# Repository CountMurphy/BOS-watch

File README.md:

Brotherhood of Steel Watch
========================

Ad Victoriam brother!

The BOS watch is the second version of my GPS enabled wristwatches. Stripped of the non used features and annoyances of the [Pipman](https://random-hackery.net/post/pipman-gps-watch/) , the BOS watch contains all things a man traveling the wastes could want

[Official Page](https://random-hackery.net/post/bos-watch/)

Features
---------------
- GPS time syncing - get local time anywhere on earth at power up

- Tilt compensated compass (with LED directional indicators and exact heading information)

- Stop watch / countdown timer

- Speaker (Plays the fallout theme!)

- TV B-gone

- A Frickn' Laser!&trade;

- Low power usage

- USB charging

-  Gieger Counter sound emulator (planned at least)

- Retro look and feel using custom DIP switches (with 7 operating modes) and 1970's era calculator display bubble LEDs

Tech
---------
The BOS watch uses an arm processor and C (Huzzah! No more awful propeller spin code)

License
----------
[DBAD](https://github.com/philsturgeon/dbad/blob/master/LICENSE-en.md)

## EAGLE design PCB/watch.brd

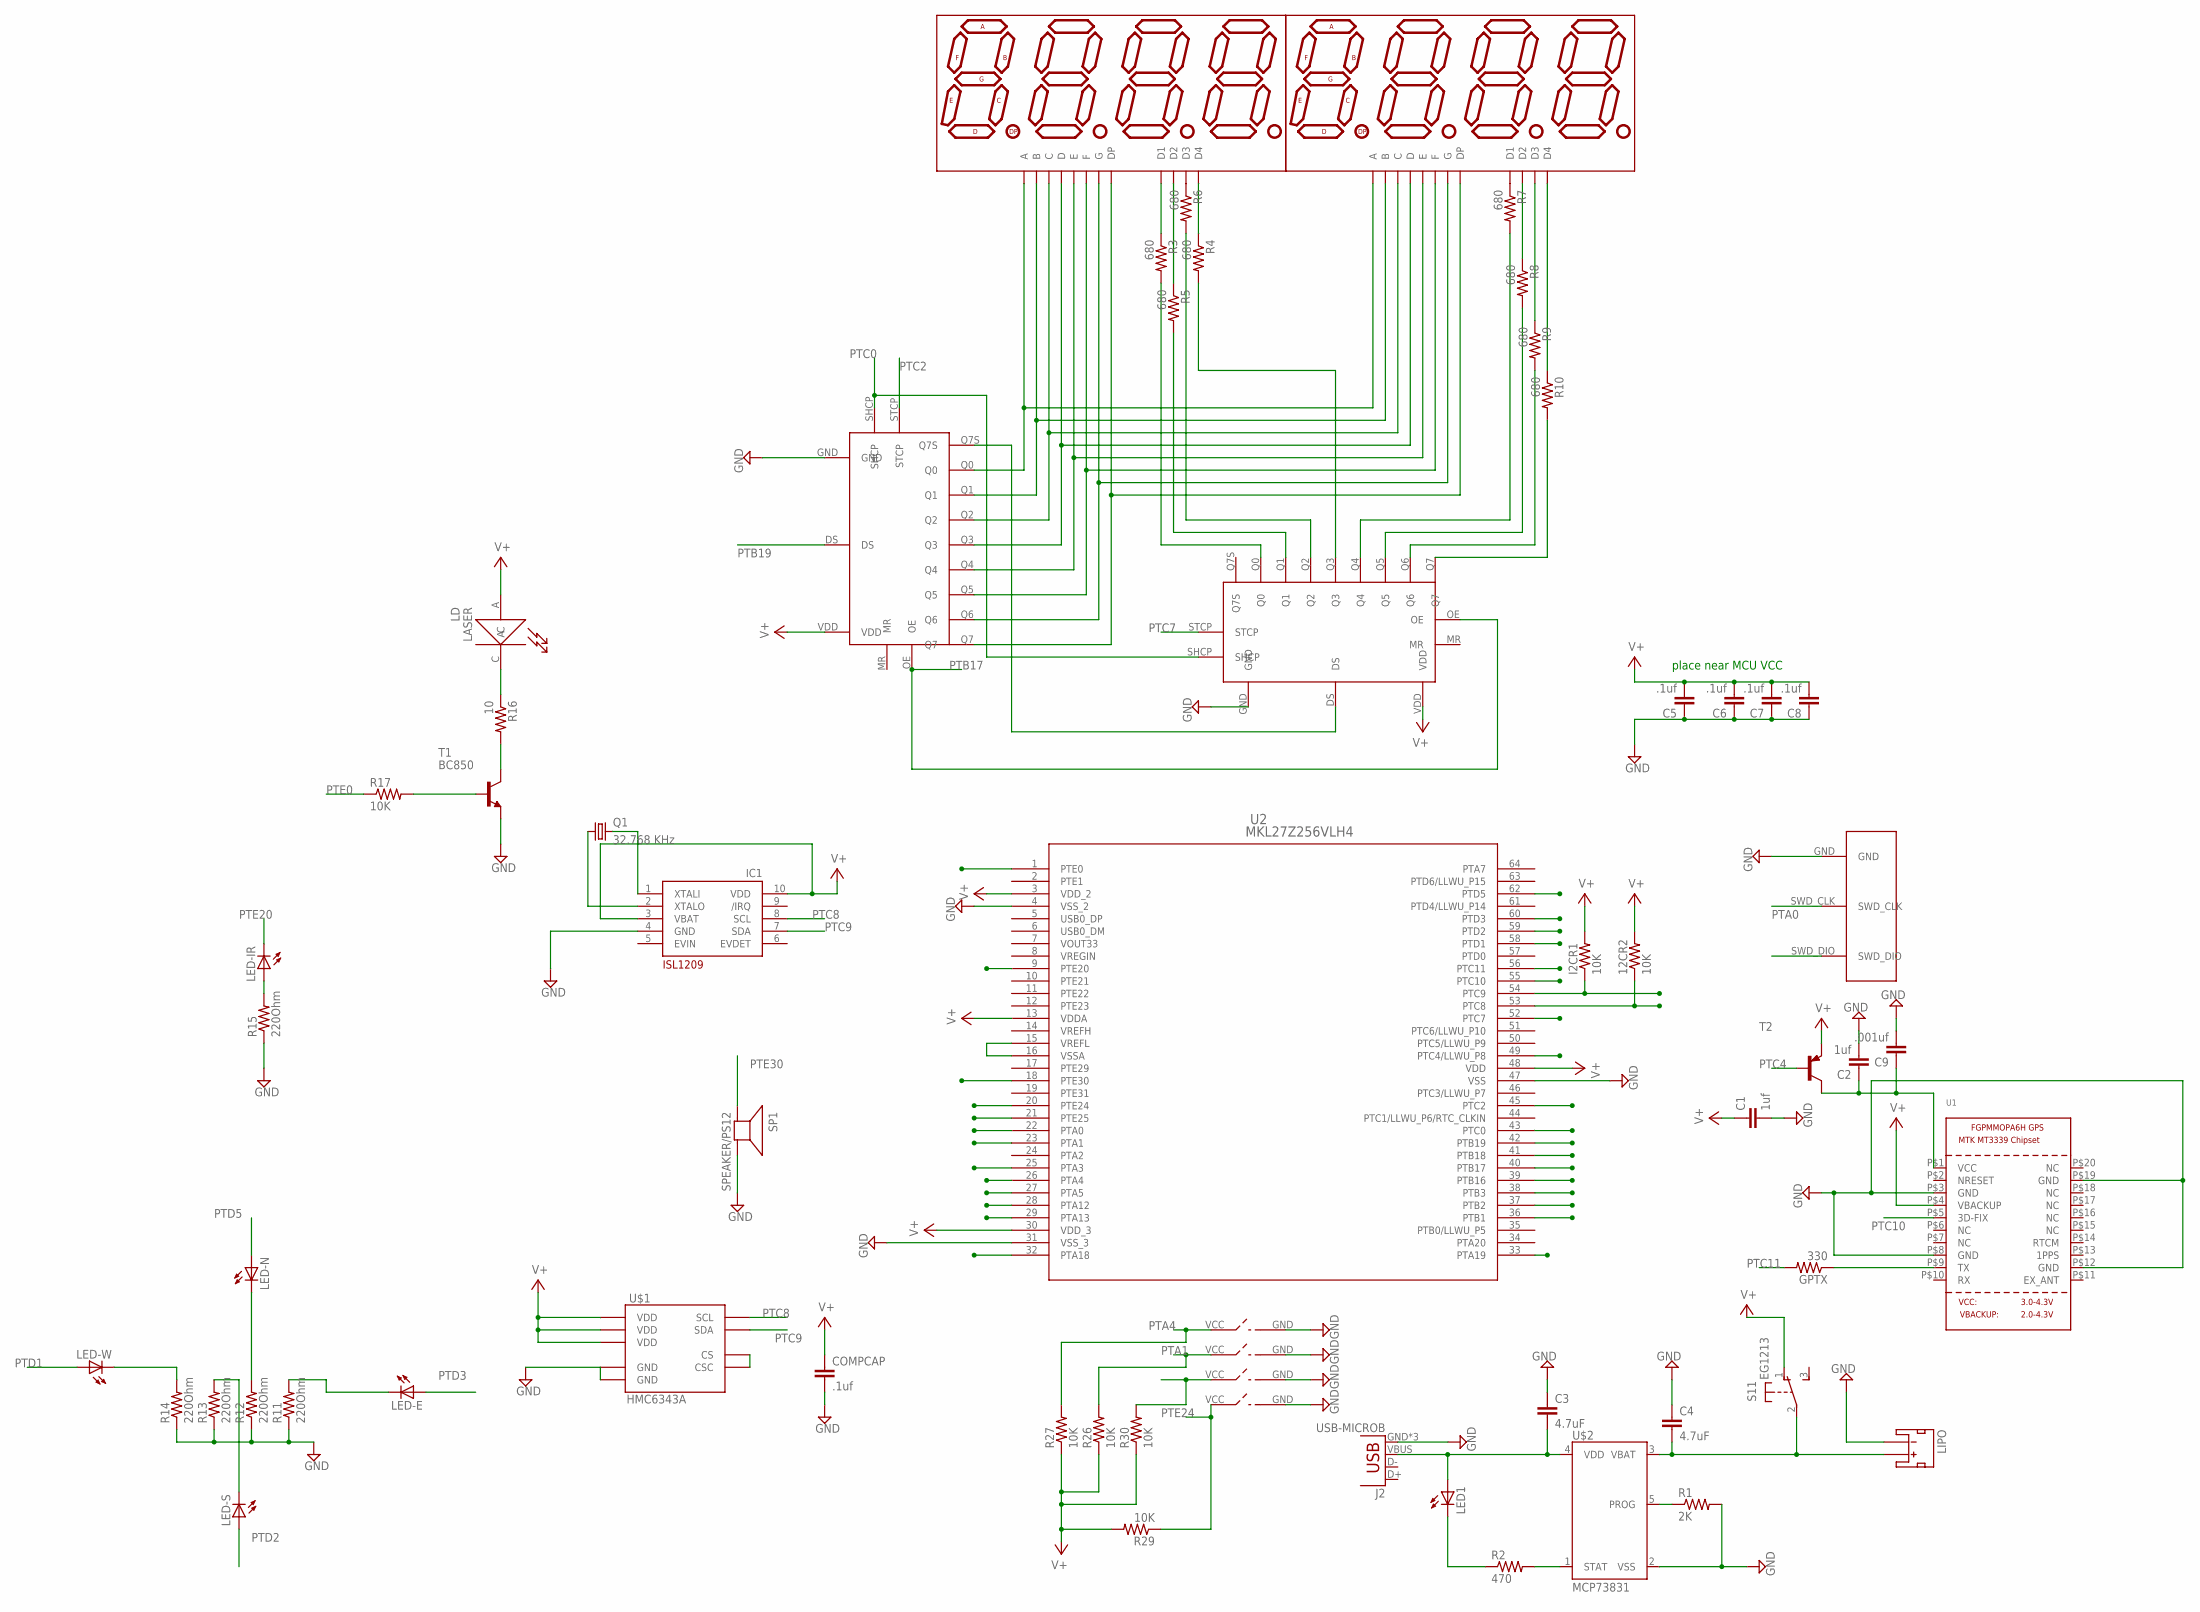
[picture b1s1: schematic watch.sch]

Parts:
12CR2: 10K; 0603-RES
C1, C2: 1uf; 0603
C3, C4: 4.7uF; 0603-CAP
C5, C6, C7, C8: .1uf; 0603
C9: .001uf; 0603
COMPCAP: .1uf; 0603
DISP1, DISP2: 7-SEGMENT-4DIGIT-COUNTER-HP-BUBBLE; DIL12
GPTX: 330; 0603-RES
I2CR1: 10K; 0603-RES
IC1: ISL1209; MSOP10
J2: USB-MICROB
LASER: LD; LD-FLUSH-WITH-JUMPER
LED1: LED_ESML0603; LED_SML0603
LED-E: LED5MM
LED-IR: LED5MM
LED-N: LED5MM
LED-S: LED5MM
LED-W: LED5MM
LIPO: JST_2MM_MALE; JST-2-SMD
Q1: 32.768 KHz; TC26H
R1: 2K; 0603-RES
R2: 470; 0603-RES
R3, R4, R5, R6, R7, R8, R9, R10: 680; 0603-RES
R11, R12, R13, R14, R15: 220Ohm; 0603-RES
R16: 10; 0603-RES
R17, R26, R27, R29, R30: 10K; 0603-RES
S1: EG1213
SP1: SPEAKER/PS12; PS12
SWD_BREAKOUT: SWD_BREAKOUTS; SWD
T1: BC850; SOT23
T2: -PNP-SOT23-EBC; SOT23-EBC
U1: GPS_FGPMMOPA6H; FGPMMOPA6H
U2: MKL27Z256VLH4; LQFP-64_10X10X1.6
U$1: HMC6343A; LCC36
U$2: MCP73831; SOT23-5
U$3, U$7, U$8, U$9: DIPS
U$4, U$5: 74HC595PW

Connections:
GND: C1.2, C2.2, C3.1, C4.1, C5.1, C6.1, C7.1, C8.1, C9.2, COMPCAP.2, IC1.4 (GND), J2.GND, J2.MT1 (GND), J2.MT2 (GND), LIPO.1 (-), R1.2, R11.1, R12.1, R13.1, R14.1, R15.1, SP1.P$2 (-), SWD_BREAKOUT.GND, T1.2 (E), U1.P$3 (GND), U1.P$8 (GND), U1.P$12 (GND), U1.P$19 (GND), U2.4 (VSS_2), U2.31 (VSS_3), U2.47 (VSS), U$1.25 (GND), U$1.29 (GND), U$2.2 (VSS), U$3.GND, U$4.GND, U$5.GND, U$7.GND, U$8.GND, U$9.GND
unnamed: U$1.22 (CS), U$1.35 (CSC)
unnamed: U2.15 (VREFL), U2.16 (VSSA)
unnamed: C4.2, LIPO.2 (+), S1.2, U$2.3 (VBAT)
unnamed: C3.2, J2.VBUS, LED1.A, U$2.4 (VDD)
unnamed: LED1.C, R2.1
unnamed: C2.1, C9.1, T2.C, U1.P$1 (VCC)
unnamed: R2.2, U$2.1 (STAT)
unnamed: R1.1, U$2.5 (PROG)
unnamed: DISP1.1 (D1), R3.1
unnamed: DISP1.10 (D2), R5.1
unnamed: DISP1.12 (A), DISP2.12 (A), U$4.Q0
unnamed: DISP1.4 (D3), R6.1
unnamed: DISP1.6 (D4), R4.1
unnamed: DISP2.1 (D1), R7.1
unnamed: DISP2.10 (D2), R8.1
unnamed: DISP1.7 (G), DISP2.7 (G), U$4.Q6
unnamed: DISP1.5 (DP), DISP2.5 (DP), U$4.Q7
unnamed: R9.2, U$5.Q6
unnamed: DISP1.9 (F), DISP2.9 (F), U$4.Q5
unnamed: DISP2.4 (D3), R9.1
unnamed: DISP1.8 (D), DISP2.8 (D), U$4.Q3
unnamed: R8.2, U$5.Q5
unnamed: R7.2, U$5.Q4
unnamed: R4.2, U$5.Q3
unnamed: R6.2, U$5.Q2
unnamed: DISP2.6 (D4), R10.1
unnamed: R3.2, U$5.Q0
unnamed: U$4.Q7S, U$5.DS
unnamed: R10.2, U$5.Q7
unnamed: GPTX.1, U1.P$9 (TX)
unnamed: R5.2, U$5.Q1
unnamed: LED-N.K (C), R12.2
unnamed: LED-E.K (C), R11.2
unnamed: LED-W.K (C), R14.2
unnamed: LED-S.K (C), R13.2
unnamed: LED-IR.A, R15.2
unnamed: LASER.C, R16.1
unnamed: R16.2, T1.3 (C)
unnamed: R17.2, T1.1 (B)
unnamed: IC1.1 (XTALI), Q1.2
unnamed: IC1.2 (XTALO), Q1.1
unnamed: DISP1.2 (E), DISP2.2 (E), U$4.Q4
unnamed: DISP1.11 (B), DISP2.11 (B), U$4.Q1
unnamed: DISP1.3 (C), DISP2.3 (C), U$4.Q2
PTA0: SWD_BREAKOUT.SWD_CLK, U2.22 (PTA0)
PTA1: R26.2, U2.23 (PTA1), U$7.VCC (V)
PTA3: SWD_BREAKOUT.SWD_DIO, U2.25 (PTA3)
PTA4: R27.2, U2.26 (PTA4), U$3.VCC (V)
PTA5: U2.27 (PTA5)
PTA12: U2.28 (PTA12)
PTA13: U2.29 (PTA13)
PTA18: U2.32 (PTA18)
PTA19: U2.33 (PTA19)
PTB1: U2.36 (PTB1)
PTB2: U2.37 (PTB2)
PTB3: U2.38 (PTB3)
PTB16: U2.39 (PTB16)
PTB17: U2.40 (PTB17), U$4.OE, U$5.OE
PTB18: U2.41 (PTB18)
PTB19: U2.42 (PTB19), U$4.DS
PTC0: U2.43 (PTC0), U$4.SHCP, U$5.SHCP
PTC2: U2.45 (PTC2), U$4.STCP
PTC4: T2.B, U2.49 (PTC4/LLWU_P8)
PTC7: U2.52 (PTC7), U$5.STCP
PTC8: 12CR2.1, IC1.8 (SCL), U2.53 (PTC8), U$1.32 (SCL)
PTC9: I2CR1.1, IC1.7 (SDA), U2.54 (PTC9), U$1.36 (SDA)
PTC10: U1.P$5 (3D-FIX), U2.55 (PTC10)
PTC11: GPTX.2, U2.56 (PTC11)
PTD1: LED-W.A, U2.58 (PTD1)
PTD2: LED-S.A, U2.59 (PTD2)
PTD3: LED-E.A, U2.60 (PTD3)
PTD5: LED-N.A, U2.62 (PTD5)
PTE0: R17.1, U2.1 (PTE0)
PTE20: LED-IR.K (C), U2.9 (PTE20)
PTE24: R29.1, U2.20 (PTE24), U$9.VCC (V)
PTE25: R30.2, U2.21 (PTE25), U$8.VCC (V)
PTE30: SP1.P$1 (+), U2.18 (PTE30)
V+: 12CR2.2, C1.1, C5.2, C6.2, C7.2, C8.2, COMPCAP.1, I2CR1.2, IC1.3 (VBAT), IC1.10 (VDD), LASER.A, R26.1, R27.1, R29.2, R30.1, S1.1 (O), T2.E, U1.P$4 (VBACKUP), U2.3 (VDD_2), U2.13 (VDDA), U2.30 (VDD_3), U2.48 (VDD), U$1.3 (VDD), U$1.11 (VDD), U$1.21 (VDD), U$4.VDD, U$5.VDD
VREFH: U2.14 (VREFH)

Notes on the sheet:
place near MCU VCC

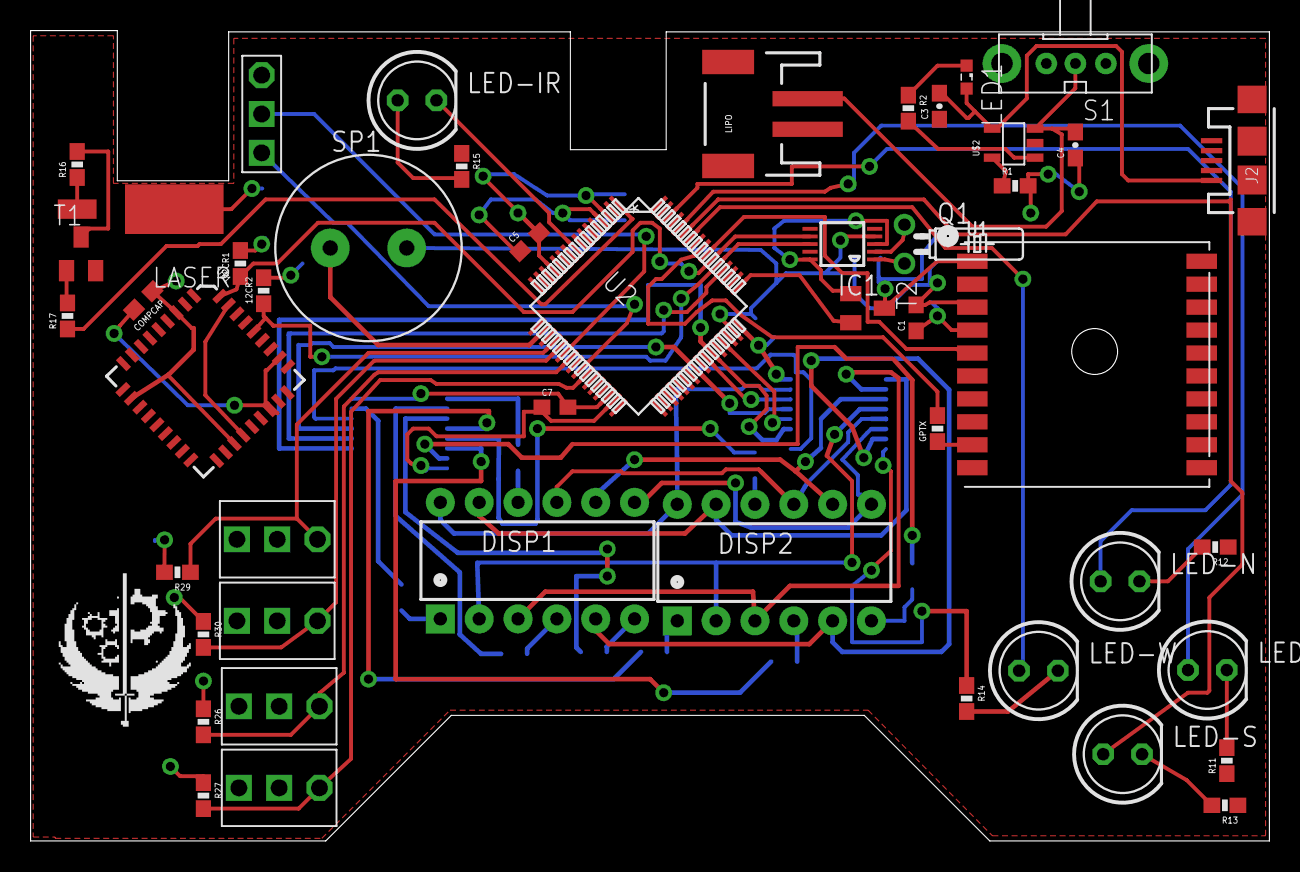
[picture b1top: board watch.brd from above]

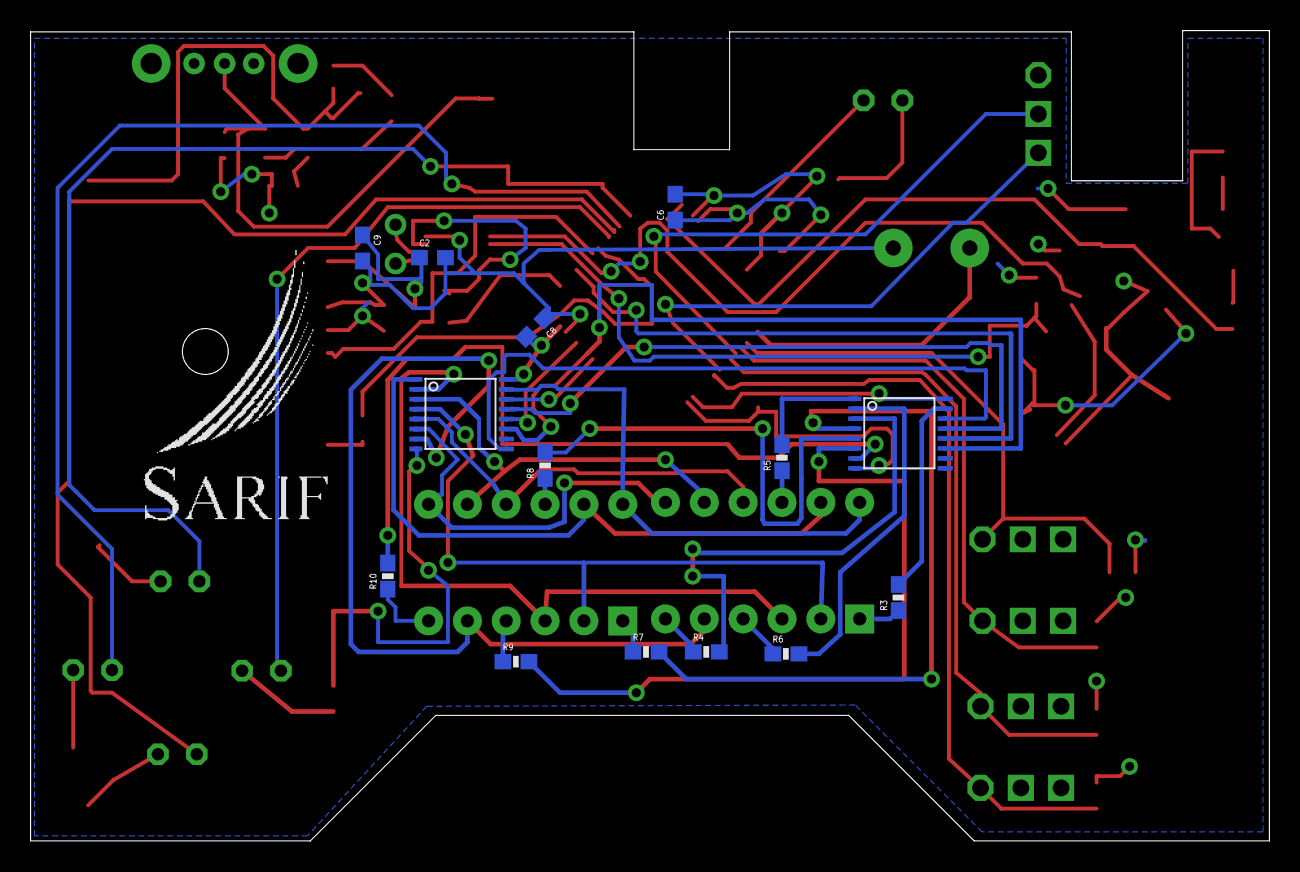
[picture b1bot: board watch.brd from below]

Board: 2 copper layers, 81.0 x 53.0 mm, 62 parts (14 on the bottom side), 69 nets.

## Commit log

2016-03-25 Added
2016-04-26 base layout
2016-04-26 made less messy, added libs
2016-04-26 wired more components
2016-04-30 added swd breakouts
2016-04-30 added charging unit
2016-05-01 added labels
2016-05-01 added pull up resistors
2016-05-20 started register lib
2016-05-20 added pads
2016-05-20 added shift regs to board
2016-05-21 finished first run of shift registers
2016-05-21 wired registers to board
2016-05-21 wired shift regs
2016-05-21 added compass leds
2016-05-21 added IR led.
2016-05-21 moved 5 way switch wiring
2016-05-22 added laser diode for lulz
2016-05-22 fixed gps fett
2016-05-22 cleaned up gps, added label for gps cap
2016-05-22 added vback cap
2016-05-22 fixed gps cap
2016-05-22 added mcu caps
2016-05-22 added readme
2016-05-22 added ssl for image
2016-05-22 added RTC crystal
2016-05-22 fixed typo in read me
2016-05-23 I think the SR clocks are now wired correctly?
2016-05-24 Moved Resistors from digit pins to segment pins and moved README image location to private server
2016-05-25 added control switch resistors
2016-07-08 reduced the amount of display resistors by more than half
2016-07-08 placement
2016-07-08 placed brd resistors
2016-07-09 added polygons
2016-07-09 top row hooked up
2016-07-09 wired most of the led display. TODO: wire SR together. God help me
2016-07-10 fixed vcc layer
2016-07-10 wired more of the SR
2016-07-19 wired all SR but one pin
2016-07-22 w00t! wired all SR
2016-07-22 cleaned up crap
2016-07-22 wired more resistors and traces
2016-08-27 wired charging circuit
2016-08-27 moved clock, rewired gps
2016-08-27 rewired gps
2016-08-27 laser wired
2016-08-27 refactored charging circuit and add caps to it
2016-08-28 wired compass LEDs. good god this thing is a mess
2016-08-28 removed airwires, added decoupling caps
2016-09-03 wired swd
2016-09-03 fixed some fuck ups
2016-09-03 moar refactoring
2016-09-05 fixed more wiring issues. started i2c
2016-09-05 fixed mroe air wires
2016-09-15 wired decoupling caps
2016-09-15 moved IR for smaller form factor
2016-09-18 all but one decoup cap done
2016-09-18 finished last decoupling cap
2016-09-27 added gps tx resistor
2016-09-27 altered values on gps caps
2016-09-27 finished adding gps caps per https://cdn-shop.adafruit.com/datasheets/GlobalTop-FGPMMOPA6H-Datasheet-V0A.pdf page 26
2016-10-18 added dip switches. need to check spaces for compass.
2016-10-18 fixed last air wire
2016-10-23 moved compass further from switches
2016-10-23 started drc
2016-10-23 more drc work
2016-10-26 more drc, discovered cockup with trace overlap
2016-10-26 overlaps fixed, reintroduced airwires
2016-11-02 fixed air wires
2016-11-18 final changes for drc
2016-11-19 added brand logo to rear (giggity)
2016-11-26 Board reshaped
2017-01-13 moved usb
2017-01-24 removed drill hole replaced with battery wire notch
2017-01-24 fixed bad dip package
2017-02-19 converted to kicad
    Eagle changed its licensing in a super dickish way. Done with that
2017-02-20 added laser warning text
2017-02-28 added clearer labels
2017-05-01 added BOM because KIcad BOM is terribad
2017-05-01 added KSDK and build scripts
2017-05-06 Added cmake files
2017-05-06 added missing gdb file for firmware upload
2017-05-06 test code
2017-05-08 test push for new git server
2017-05-08 removed garbage files
2017-05-09 compass test code, halts after send
2017-05-10 more testing
2017-05-10 added i2c thing
2017-05-10 fixed stupid sdk copy
2017-05-27 got i2c working
2017-06-06 minor improvments
2017-06-06 fixed spi1
2017-06-06 fixed resistor vals
2017-06-06 fixed uart gps
2017-06-07 moved OE to a timer pin to control display brightness
2017-06-07 removed large retarded vias to better enable trace navigation
2017-06-07 wired storage clock together for SR
2017-06-08 fixed laser label
2017-06-09 fixed compass orientation
2017-06-09 fixed clock crystal
2017-10-08 blinken lights
2017-10-08 seperated logic
2017-10-08 removed warnings
2017-12-21 added char dictionary
2017-12-21 refactored
2017-12-21 added add decimal method
2017-12-21 display is working
2017-12-21 removed warnings and unneeded code
2017-12-25 lower case g
2017-12-25 1st part of centering done
2017-12-27 at horse shit solution
2017-12-27 feels close
2017-12-27 feels close2
2017-12-27 evens work, not odds
2017-12-27 odds work
2018-01-01 multiplexing works, but is dim
2018-01-01 a tad brighter now
2018-01-16 made screen less nausiating
2018-01-17 added through hole usb
2018-01-17 fixed bad reset on SRs
2018-01-18 reversed IR LED
2018-01-18 fixed pnp
2018-01-21 fixed Laser npn, fixed laser and led south from bridge
2018-01-22 fixed labels
2018-02-13 plays fallout theme song
2018-02-13 turned screen back on
2018-02-13 added buzzer files I forgot to include (oops)
2018-03-10 added Y to dictionary
2018-03-28 updated ignore
2018-03-31 Added RTC functions
2018-04-26 Added GPS and refactored bad code
2018-05-02 clock menu done
2018-05-02 Added switch menu system
2018-05-02 RAD reader online
2018-05-02 fixed heisenbug
2018-05-02 can now interrupt song
2018-05-03 now prompts for dst
2018-05-06 Added scrolling text
2018-05-06 gps Menu done. Test release mode!!!
2018-05-08 Compass Modes added
2018-05-08 removed compiler warning
2018-05-09 stop watch works
2018-05-12 Added Count down timer
2018-05-14 refactored code. issue #5
2018-05-14 added laser code, but laser will not fire. Hardware issue
2018-05-20 added case
2018-05-20 mocked board
2018-05-23 Created Botton of case
2018-05-31 fixed debug gps bug
2018-07-25 compass directional LEDs fixed
2018-07-26 added pwr options, but going to HIGH from anything destroys the buzzer
2018-07-26 added pwr management definitions
2018-07-26 fixed compass again
2018-07-26 Completed Case Work
2018-08-04 fixed date parse bug
2018-08-04 gps case adjust for second build
2018-08-07 shorted led cover
2018-08-09 fixed compass power bleed
2018-09-25 Fixed date parsing, again
2018-10-13 typo in url
2018-10-26 fixed countdown display over 10
2018-10-30 forgot to convert to ascii
2018-11-16 refactored maths
2019-01-23 tweaked battery depth in case
2019-01-24 added low power mode request option on boot
2019-01-24 fixed power drain on standby.
2019-01-26 added removed display line
2019-01-26 fixed date flicker
2019-01-26 fixed compass heading precision
2019-01-26 added take on me
2019-01-27 fixed easily breakable screw
2019-02-02 removed low power flicker
2019-02-02 added pnp resistor
2019-02-04 added home page
2019-02-04 spelling
2019-03-02 Fixed GPS non display bug
2019-03-05 added case nub to prevent opening
2019-06-16 added tilt detection
2019-07-14 Revert "added tilt detection" was supposed to save battery...it doesn't
    This reverts commit f5f9ec7ae5f1f808401d766e55b7d08ef72a9010.
2019-08-16 Upated link
2023-08-30 added half mil spacer

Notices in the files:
parts and their libraries:
SparkFun-Resistors: Licensing: Creative Commons ShareAlike 4.0 International - https://creativecommons.org/licenses/by-sa/4.0
